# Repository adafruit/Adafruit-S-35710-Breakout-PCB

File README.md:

## Adafruit S-35710 Low-Power Wake Up Timer Breakout - STEMMA QT / Qwiic PCB

<a href="http://www.adafruit.com/products/5959"><br/>
Click here to purchase one from the Adafruit shop</a>

PCB files for the Adafruit S-35710 Low-Power Wake Up Timer Breakout - STEMMA QT / Qwiic. 

Format is EagleCAD schematic and board layout
* https://www.adafruit.com/product/5959

### Description

The Adafruit S-35710 Wake Up Timer is a low power 'watchdog timer' chip that can be programmed to alert with a digitally-configurable alarm from 1 second up to 194 days, thanks to a 24-bit second counter. It's an interesting alternative to a real time clock or internal sleep timer and might be useful for some ultra-low-power projects that want to have a separate (and possibly separately-powered) chip to handle time-keeping and alarms. We covered this component on EYE ON NPI and thought it would make for a nice breakout in the shop.

Usage is pretty simple: on I2C write of the timer register, the chip starts counting from 0 seconds up and the OUT pin goes high. When the count matches the timer register, the OUT pin goes low. Simple, and like we mentioned, it's very low power, drawing only 0.2uA. The output is open-drain, and if you want to have it be inverted, there's a switch that will put the signal through an N-channel FET so the polarity goes the other way.

One thing to note, is that on power-up the OUT line is default low, which means its not good for a low-power sleep manager, only for watch-dog-like timings. That is to say, you cannot connect this to your microcontroller's reset or enable line to self-depower because it will be disabled/reset when powered up. Still, maybe a useful chip for some folks who want to signal after a long delay or have a more complex power management scheme.

To get you going fast, we spun up a custom-made PCB in the STEMMA QT form factor, making it easy to interface with. The STEMMA QT connectors on either side are compatible with the SparkFun Qwiic I2C connectors. This allows you to make solderless connections between your development board and the S-35710 or to chain it with a wide range of other sensors and accessories using a compatible cable.

### License

Adafruit invests time and resources providing this open source design, please support Adafruit and open-source hardware by purchasing products from [Adafruit](https://www.adafruit.com)!

Designed by Limor Fried/Ladyada for Adafruit Industries.

Creative Commons Attribution/Share-Alike, all text above must be included in any redistribution. 
See license.txt for additional details.

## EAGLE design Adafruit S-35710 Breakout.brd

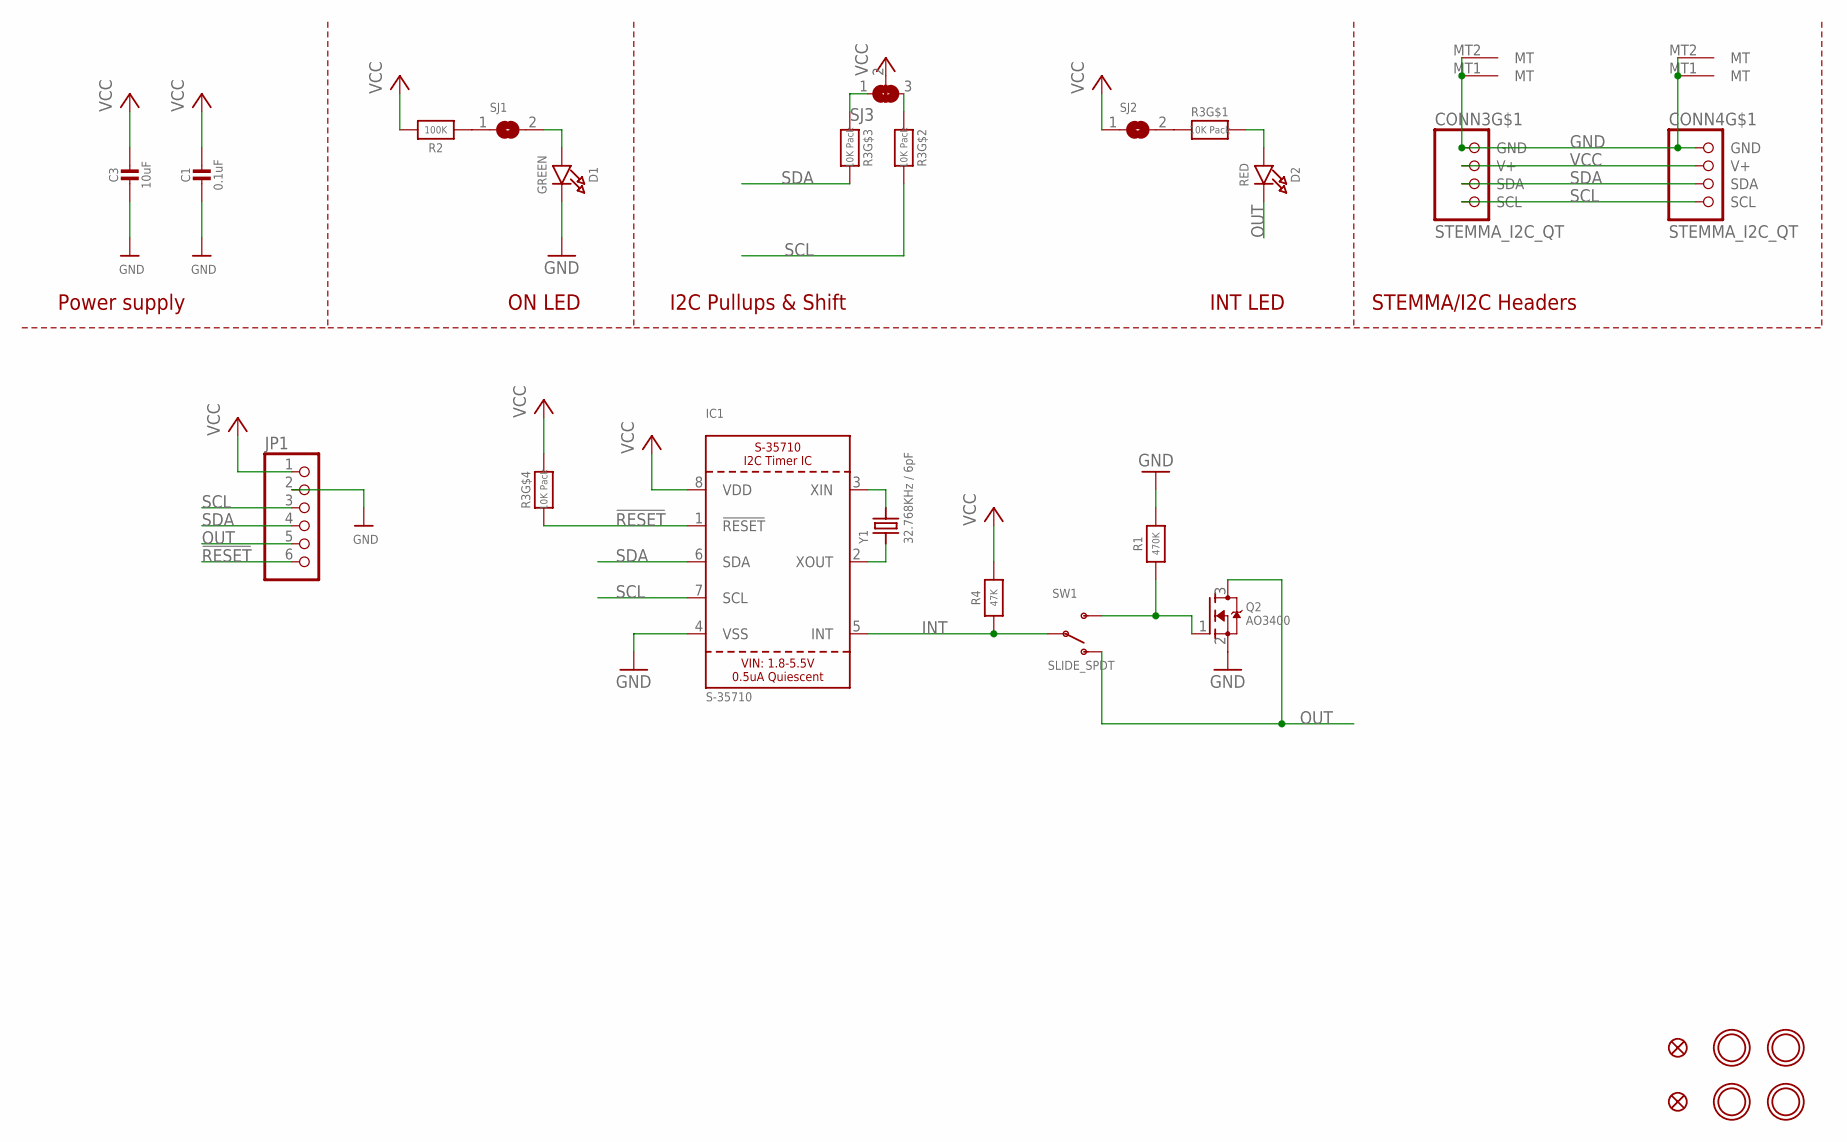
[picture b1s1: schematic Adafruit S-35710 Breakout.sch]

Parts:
C1: 0.1uF; 0603-NO
C3: 10uF; 0805-NO
CONN3, CONN4: STEMMA_I2C_QT; JST_SH4
D1: GREEN; CHIPLED_0603_NOOUTLINE
D2: RED; CHIPLED_0603_NOOUTLINE
FID3, FID4: FIDUCIAL_1MM
IC1: S-35710; MSOP8_0.65MM
JP1: HEADER-1X670MIL; 1X06_ROUND_70
Q2: AO3400; SOT23-WIDE
R1: 470K; 0603-NO
R2: 100K; 0603-NO
R3: 10K Pack; RESPACK_4X0603
R4: 47K; 0603-NO
SJ1, SJ2: SOLDERJUMPERCLOSED; SOLDERJUMPER_CLOSEDWIRE
SJ3: SOLDERJUMPER_2WAY; SOLDERJUMPER_2WAY_OPEN_NOPASTE
SW1: SLIDE_SPDT; SPDT_SMT_SSSS811101
U$1, U$17, U$19, U$21: MOUNTINGHOLE2.5; MOUNTINGHOLE_2.5_PLATED
Y1: 32.768KHz / 6pF; XTAL3215

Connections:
!RESET: IC1.1 (!RESET), JP1.6, R3.4 (1)
GND: C1.2, C3.2, CONN3.1 (GND), CONN3.MT1 (MT), CONN3.MT2 (MT), CONN4.1 (GND), CONN4.MT1 (MT), CONN4.MT2 (MT), D1.C, IC1.4 (VSS), JP1.2, Q2.2 (S), R1.2
INT: IC1.5 (INT), R4.1, SW1.B
unnamed: D1.A, SJ1.2
unnamed: R3.1, SJ2.2
unnamed: R2.1, SJ1.1
unnamed: D2.A, R3.8 (2)
unnamed: IC1.3 (XIN), Y1.P$2 (2)
unnamed: IC1.2 (XOUT), Y1.P$1 (1)
unnamed: R3.3 (1), SJ3.1
unnamed: Q2.1 (G), R1.1, SW1.C (S)
unnamed: R3.2 (1), SJ3.3
OUT: D2.C, JP1.5, Q2.3 (D), SW1.A (O)
SCL: CONN3.4 (SCL), CONN4.4 (SCL), IC1.7 (SCL), JP1.3, R3.7 (2)
SDA: CONN3.3 (SDA), CONN4.3 (SDA), IC1.6 (SDA), JP1.4, R3.6 (2)
VCC: C1.1, C3.1, CONN3.2 (V+), CONN4.2 (V+), IC1.8 (VDD), JP1.1, R2.2, R3.5 (2), R4.2, SJ2.1, SJ3.2

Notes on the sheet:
I2C Pullups & Shift
STEMMA/I2C Headers
ON LED
Power supply
INT LED

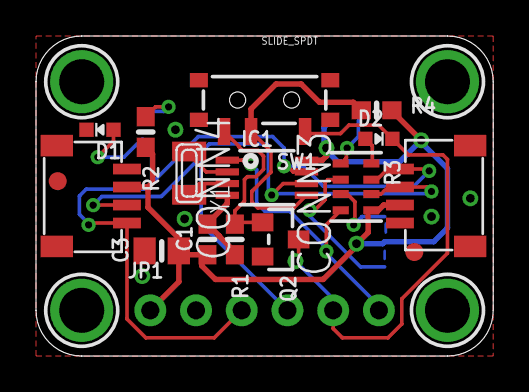
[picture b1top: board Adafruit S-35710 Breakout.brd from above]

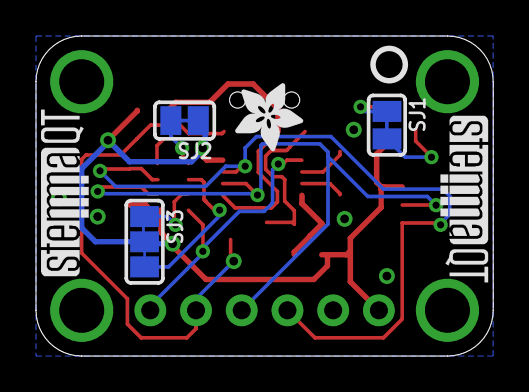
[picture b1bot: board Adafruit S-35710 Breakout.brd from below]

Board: 2 copper layers, 25.4 x 17.8 mm, 47 parts (15 on the bottom side), 16 nets.

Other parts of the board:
PLABEL0: PLABEL0
PLABEL1: PLABEL1
PLABEL2: PLABEL2
PLABEL3: PLABEL3
PLABEL4: PLABEL4
PLABEL5: PLABEL5
PLABEL6: PLABEL6
PLABEL7: PLABEL7
PLABEL8: PLABEL8
PLABEL9: PLABEL9
PLABEL10: PLABEL10
PLABEL11: PLABEL11
PLABEL13: PLABEL13
PLABEL14: PLABEL14
PLABEL15: PLABEL15
PLABEL16: PLABEL16
PLABEL17: PLABEL17
PLABEL18: PLABEL18
PLABEL19: PLABEL19
U$22: ADAFRUIT_3.5MM
U$25: PCBFEAT-REV-040
U$30, U$31: STEMMAQT

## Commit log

2024-05-08 cookiecutter

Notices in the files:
parts and their libraries:
microbuilder: This work is placed in the public domain, and may be freely used for commercial and non-commercial work with the following conditions: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
